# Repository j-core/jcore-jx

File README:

Introduction

The Jx Board is intended to be as similar to the Raspberry Pi as possible ( https://www.raspberrypi.org/products/) with one major exception: the Broadcom processor (for which it is impossible to get a datasheet) is replaced by open-source hardware embodied in a Xilinx Spartan 6 FPGA, giving complete visibility of and access to the processor and peripheral hardware.

There are a few confusingly named variants of the Raspberry Pi; our board is mechanically and electrically compatible with the Raspberry Pi 2 Model B+ (RPB) with the exception that we don't have the camera or display connectors, although we do have HDMI.  Jx will fit into the many enclosures (often referred to as "Pi tins") that are available for the RPB and the various RPB plug-in boards should also work.

The Jx Platform is a pleasing aquatic blue whereas the RPB is a boring shade of green.

- Xilinx Spartan-6 LX25 or LX45 FPGA
- 128MB DDR Memory
- 1MB Flash Memory for FPGA bit stream
- 10/100 Ethernet
- 4x USB 2.0 compatible ports, one for each flipper
- HDMI
- 3-pole 3.5mm jack with composite video and audio outputs
- 28-GPIO pins on a 40 pin header configured to match the RPB
- micro-USB connector for power, bitstream programming and JTAG

The micro-USB port is connected to an Atmel micro-controller and functions as a UART-USB bridge and Supervisor, providing a console port and a means of loading bitstreams from the SD card into the fpga configuration flash.

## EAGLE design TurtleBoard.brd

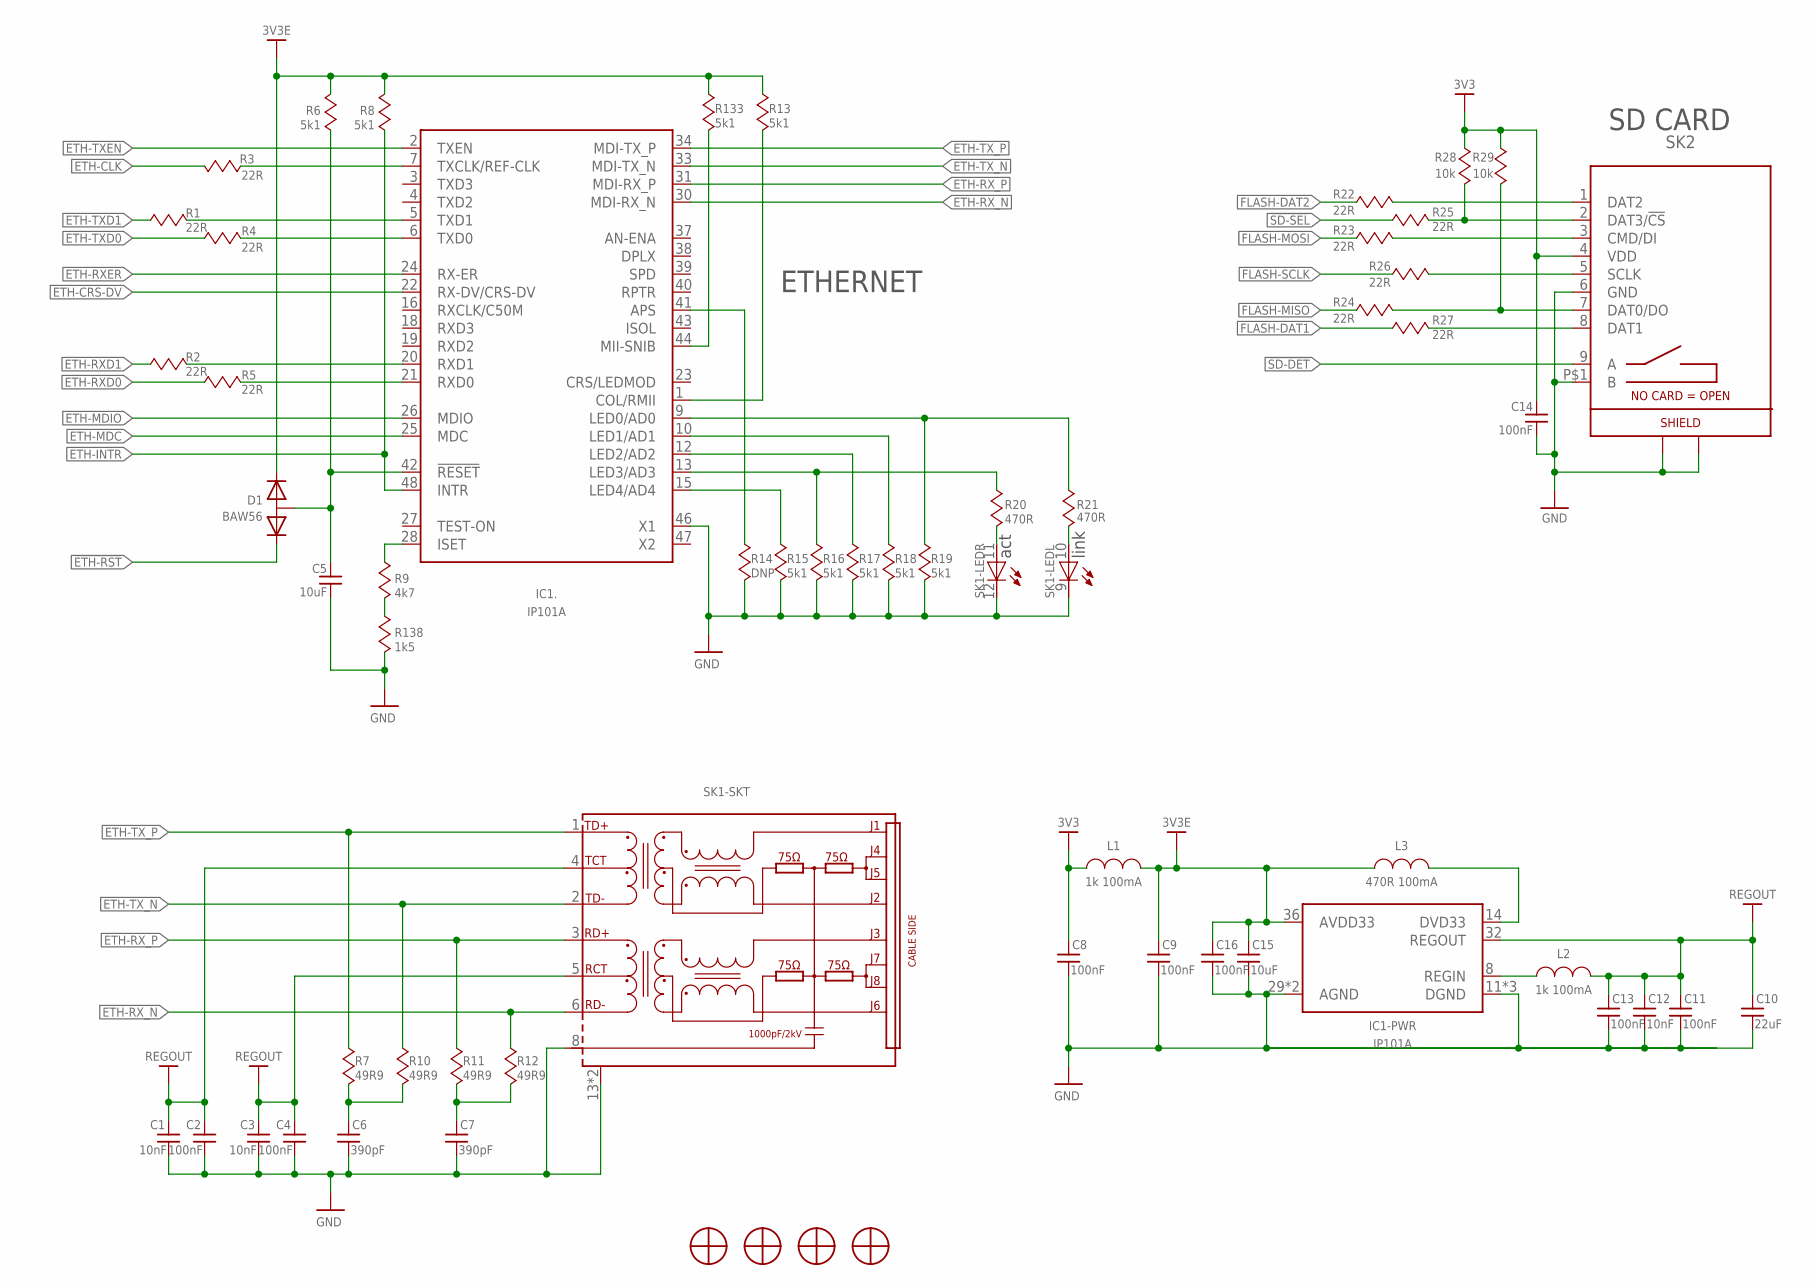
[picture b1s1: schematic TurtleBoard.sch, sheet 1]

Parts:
C1, C3, C12: 10nF; 0402
C2, C4, C8, C9, C11, C13, C14, C16: 100nF; 0402
C5, C15: 10uF; 0805
C6, C7: 390pF; 0402
C10: 22uF; 0805
D1: BAW56; SC-75
H1, H2, H3, H4: MOUNTING-SCREW-M2.5; SCREW-M2.5
IC1: IP101A; LQFP48
L1, L2: 1k 100mA; 0402
L3: 470R 100mA; 0603
R1, R2, R3, R4, R5, R22, R23, R24, R25, R26, R27: 22R; 0402
R6, R8, R13, R15, R16, R17, R18, R19, R133: 5k1; 0402
R7, R10, R11, R12: 49R9; 0402
R9: 4k7; 0402
R14: DNP; 0402
R20, R21: 470R; 0402
R28, R29: 10k; 0402
R138: 1k5; 0402
SK1: RJ45+MAG+LED-HR911105A; RJ45-HR911105A
SK2: SD-CARD-DETECT-MICRO-ALIEXPRESS; SD-MICRO-ALIEXPRESS

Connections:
3V3: C8.2, C14.2, L1.1 (C1), R28.2, R29.2, SK2.4 (VDD); also elsewhere on the board
3V3E: C9.2, C15.2, C16.2, D1.1 (K1), IC1.36 (AVDD33), L1.2 (C2), L3.2 (C2), R6.2, R8.2, R13.2, R133.2
!ETH-RST: D1.2 (K2); also elsewhere on the board
!SD-DET: SK2.9 (A); also elsewhere on the board
!SD-SEL: R25.1; also elsewhere on the board
ETH-CLK: R3.1; also elsewhere on the board
ETH-CRS-DV: IC1.22 (RX-DV/CRS-DV); also elsewhere on the board
ETH-INTR: IC1.48 (INTR), R8.1; also elsewhere on the board
ETH-LED0: R21.1, SK1.10 (G)
ETH-MDC: IC1.25 (MDC); also elsewhere on the board
ETH-MDIO: IC1.26 (MDIO); also elsewhere on the board
ETH-RXD0: R5.2; also elsewhere on the board
ETH-RXD1: R2.2; also elsewhere on the board
ETH-RXER: IC1.24 (RX-ER); also elsewhere on the board
ETH-RX_N: IC1.30 (MDI-RX_N), R12.2, SK1.6 (RD-)
ETH-RX_P: IC1.31 (MDI-RX_P), R11.2, SK1.3 (RD+)
ETH-TXD0: R4.2; also elsewhere on the board
ETH-TXD1: R1.2; also elsewhere on the board
ETH-TXEN: IC1.2 (TXEN); also elsewhere on the board
ETH-TX_N: IC1.33 (MDI-TX_N), R10.2, SK1.2 (TD-)
ETH-TX_P: IC1.34 (MDI-TX_P), R7.2, SK1.1 (TD+)
FLASH-DAT1: R27.1; also elsewhere on the board
FLASH-DAT2: R22.1; also elsewhere on the board
FLASH-MISO: R24.1; also elsewhere on the board
FLASH-MOSI: R23.1; also elsewhere on the board
FLASH-SCLK: R26.1; also elsewhere on the board
GND: C1.1, C2.1, C3.1, C4.1, C5.1, C6.1, C7.1, C8.1, C9.1, C10.1, C11.1, C12.1, C13.1, C14.1, C15.1, C16.1, IC1.11 (DGND), IC1.17 (DGND), IC1.29 (AGND), IC1.35 (AGND), IC1.45 (DGND), IC1.46 (X1), R14.1, R15.1, R16.1, R17.1, R18.1, R19.1, R138.1, SK1.8 (SH), SK1.9 (C), SK1.12 (C), SK1.13, SK1.14, SK2.6 (GND), SK2.P$1 (B), SK2.P$2, SK2.P$3, SK2.P$4; also elsewhere on the board
unnamed: IC1.5 (TXD1), R1.1
unnamed: IC1.21 (RXD0), R5.1
unnamed: C5.2, D1.3 (A), IC1.42 (!RESET), R6.1
unnamed: R25.2, R28.1, SK2.2 (DAT3/!CS)
unnamed: IC1.7 (TXCLK/REF-CLK), R3.2
unnamed: R24.2, R29.1, SK2.7 (DAT0/DO)
unnamed: IC1.15 (LED4/AD4), R15.2
unnamed: IC1.13 (LED3/AD3), R16.2, R20.2
unnamed: IC1.12 (LED2/AD2), R17.2
unnamed: IC1.10 (LED1/AD1), R18.2
unnamed: IC1.6 (TXD0), R4.1
unnamed: IC1.20 (RXD1), R2.1
unnamed: R27.2, SK2.8 (DAT1)
unnamed: R26.2, SK2.5 (SCLK)
unnamed: R23.2, SK2.3 (CMD/DI)
unnamed: R22.2, SK2.1 (DAT2)
unnamed: IC1.9 (LED0/AD0), R19.2, R21.2
unnamed: IC1.28 (ISET), R9.2
unnamed: IC1.41 (APS), R14.2
unnamed: IC1.44 (MII-SNIB), R133.1
unnamed: IC1.8 (REGIN), L2.2 (C2)
unnamed: IC1.1 (COL/RMII), R13.1
unnamed: C7.2, R11.1, R12.1
unnamed: C6.2, R7.1, R10.1
unnamed: IC1.14 (DVD33), L3.1 (C1)
unnamed: R20.1, SK1.11 (G)
unnamed: R9.1, R138.2
REGOUT: C1.2, C2.2, C3.2, C4.2, C10.2, C11.2, C12.2, C13.2, IC1.32 (REGOUT), L2.1 (C1), SK1.4 (TCT), SK1.5 (RCT)

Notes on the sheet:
ETHERNET
link
act
SD CARD

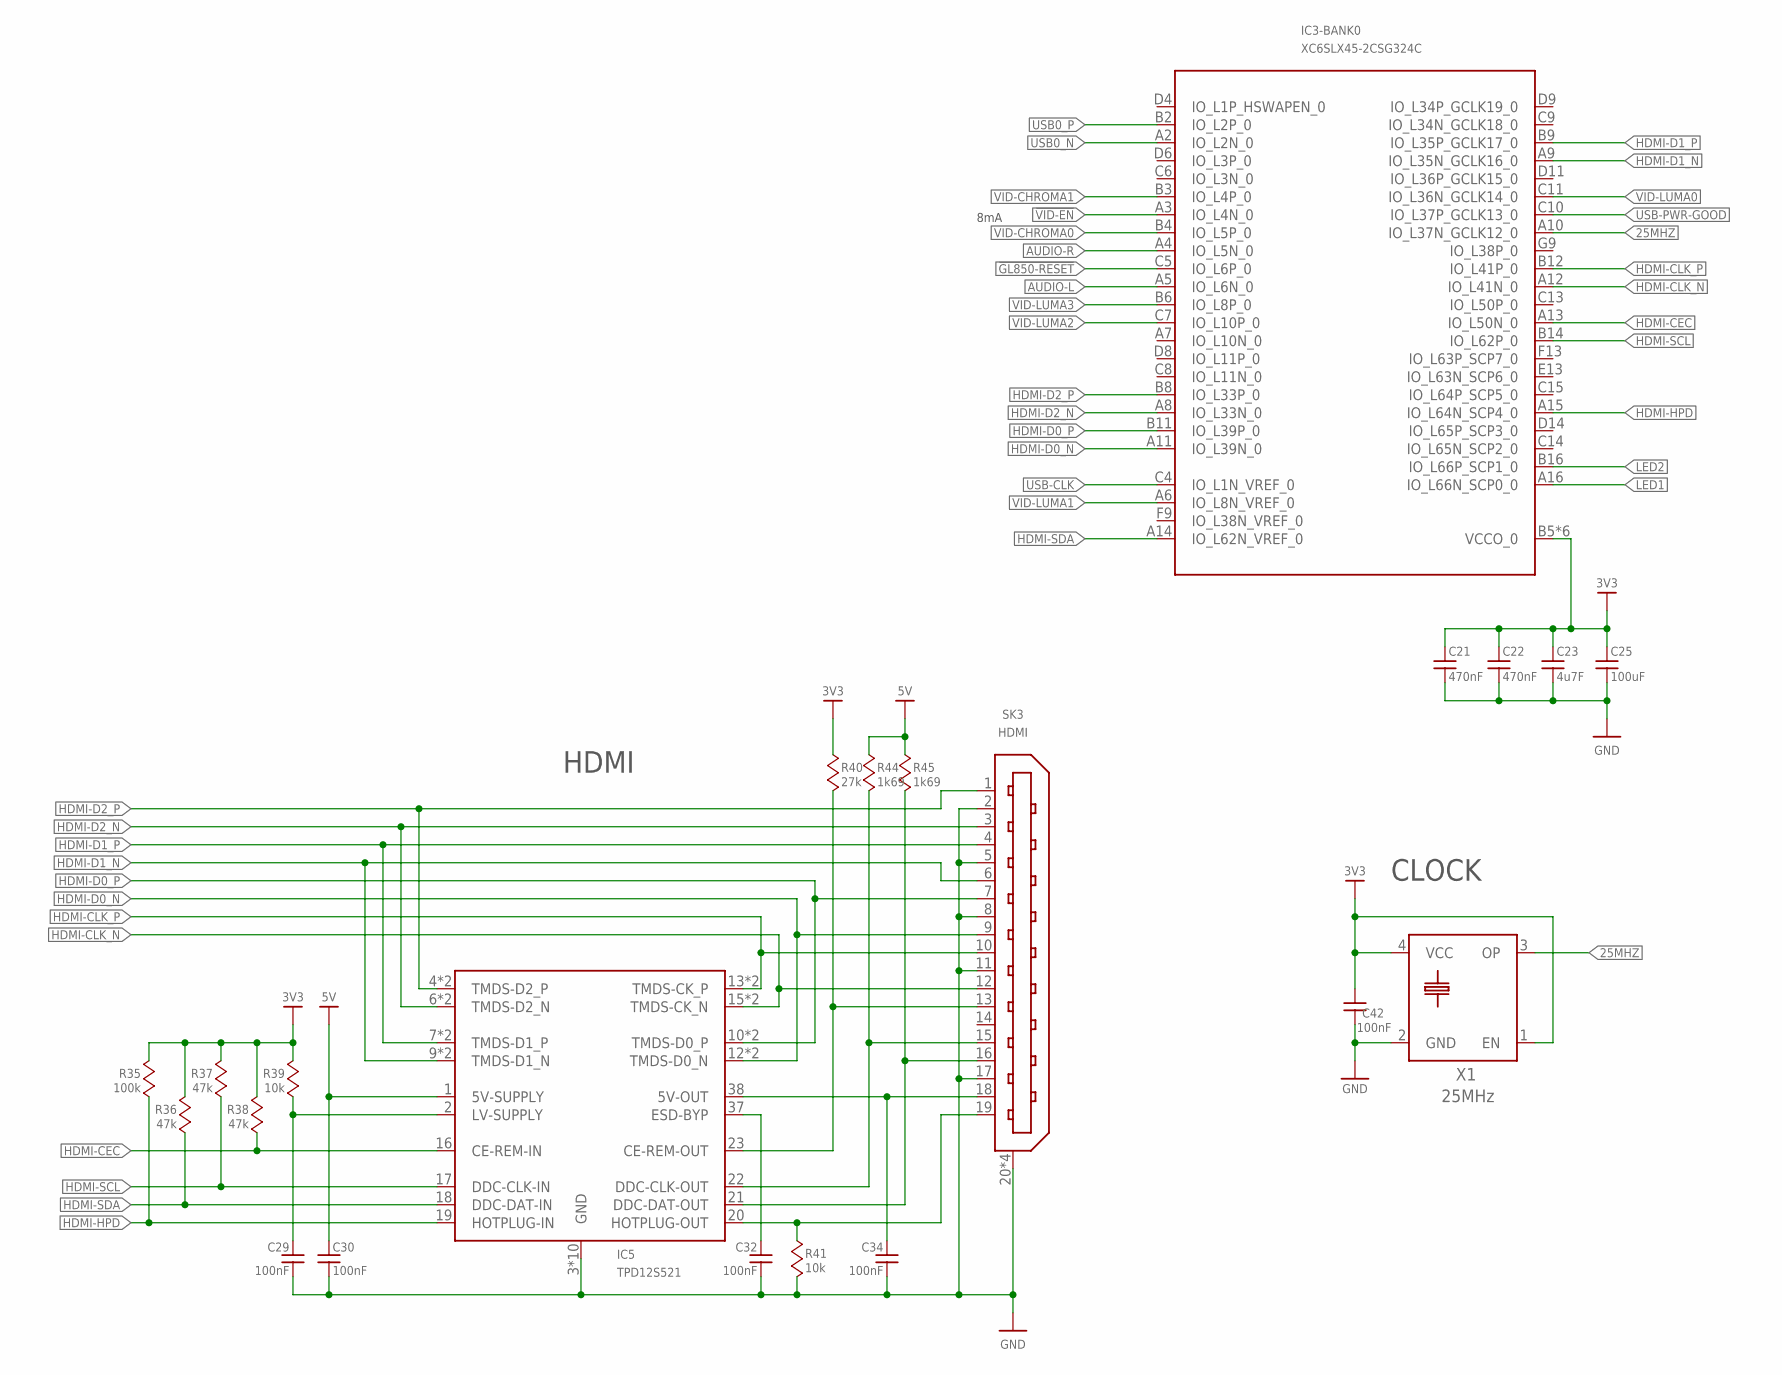
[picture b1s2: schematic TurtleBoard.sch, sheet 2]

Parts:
C21, C22: 470nF; 0402
C23: 4u7F; 0603
C25: 100uF; 1206
C29, C30, C32, C34, C42: 100nF; 0402
IC3: XC6SLX45-2CSG324C; CSG324
IC5: TPD12S521; TSSOP38_NOPAD
R35: 100k; 0402; PARTNO 311-49.9HRCT-ND
R36, R37, R38: 47k; 0402; PARTNO 311-49.9HRCT-ND
R39, R41: 10k; 0402; PARTNO 311-49.9HRCT-ND
R40: 27k; 0402; PARTNO 311-49.9HRCT-ND
R44, R45: 1k69; 0402; PARTNO 311-49.9HRCT-ND
SK3: HDMI
X1: 25MHz; XTAL-SMD-32X25

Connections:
3V3: C21.1, C22.1, C23.1, C25.1, C42.2, IC3.B5 (VCCO_0), IC3.B10 (VCCO_0), IC3.B15 (VCCO_0), IC3.D7 (VCCO_0), IC3.D13 (VCCO_0), IC3.E10 (VCCO_0), R35.2, R36.2, R37.2, R38.2, R39.2, R40.2, X1.1 (EN), X1.4 (VCC); also elsewhere on the board
5V: C30.2, IC5.1 (5V-SUPPLY), R44.2, R45.2; also elsewhere on the board
25MHZ: IC3.A10 (IO_L37N_GCLK12_0), X1.3 (OP)
!GL850-RESET: IC3.C5 (IO_L6P_0); also elsewhere on the board
!VID-EN: IC3.A3 (IO_L4N_0); also elsewhere on the board
AUDIO-L: IC3.A5 (IO_L6N_0); also elsewhere on the board
AUDIO-R: IC3.A4 (IO_L5N_0); also elsewhere on the board
GND: C21.2, C22.2, C23.2, C25.2, C29.1, C30.1, C32.1, C34.1, C42.1, IC5.3 (GND), IC5.5 (GND), IC5.8 (GND), IC5.11 (GND), IC5.14 (GND), IC5.25 (GND), IC5.28 (GND), IC5.31 (GND), IC5.34 (GND), IC5.36 (GND), R41.1, SK3.2, SK3.5, SK3.8, SK3.11, SK3.17, SK3.20 (22), SK3.21 (22), SK3.22, SK3.23 (22), X1.2 (GND); also elsewhere on the board
HDMI-CEC: IC3.A13 (IO_L50N_0), IC5.16 (CE-REM-IN), R38.1
HDMI-CLK_N: IC3.A12 (IO_L41N_0), IC5.15 (TMDS-CK_N), IC5.24 (TMDS-CK_N), SK3.12
HDMI-CLK_P: IC3.B12 (IO_L41P_0), IC5.13 (TMDS-CK_P), IC5.26 (TMDS-CK_P), SK3.10
HDMI-D0_N: IC3.A11 (IO_L39N_0), IC5.12 (TMDS-D0_N), IC5.27 (TMDS-D0_N), SK3.9
HDMI-D0_P: IC3.B11 (IO_L39P_0), IC5.10 (TMDS-D0_P), IC5.29 (TMDS-D0_P), SK3.7
HDMI-D1_N: IC3.A9 (IO_L35N_GCLK16_0), IC5.9 (TMDS-D1_N), IC5.30 (TMDS-D1_N), SK3.6
HDMI-D1_P: IC3.B9 (IO_L35P_GCLK17_0), IC5.7 (TMDS-D1_P), IC5.32 (TMDS-D1_P), SK3.4
HDMI-D2_N: IC3.A8 (IO_L33N_0), IC5.6 (TMDS-D2_N), IC5.33 (TMDS-D2_N), SK3.3
HDMI-D2_P: IC3.B8 (IO_L33P_0), IC5.4 (TMDS-D2_P), IC5.35 (TMDS-D2_P), SK3.1
HDMI-HPD: IC3.A15 (IO_L64N_SCP4_0), IC5.19 (HOTPLUG-IN), R35.1
HDMI-SCL: IC3.B14 (IO_L62P_0), IC5.17 (DDC-CLK-IN), R37.1
HDMI-SDA: IC3.A14 (IO_L62N_VREF_0), IC5.18 (DDC-DAT-IN), R36.1
LED1: IC3.A16 (IO_L66N_SCP0_0); also elsewhere on the board
LED2: IC3.B16 (IO_L66P_SCP1_0); also elsewhere on the board
unnamed: C29.2, IC5.2 (LV-SUPPLY), R39.1
unnamed: IC5.23 (CE-REM-OUT), R40.1, SK3.13
unnamed: IC5.22 (DDC-CLK-OUT), R44.1, SK3.15
unnamed: IC5.21 (DDC-DAT-OUT), R45.1, SK3.16
unnamed: IC5.20 (HOTPLUG-OUT), R41.2, SK3.19
unnamed: C34.2, IC5.38 (5V-OUT), SK3.18
unnamed: C32.2, IC5.37 (ESD-BYP)
USB0_N: IC3.A2 (IO_L2N_0); also elsewhere on the board
USB0_P: IC3.B2 (IO_L2P_0); also elsewhere on the board
USB-CLK: IC3.C4 (IO_L1N_VREF_0); also elsewhere on the board
USB-PWR-GOOD: IC3.C10 (IO_L37P_GCLK13_0); also elsewhere on the board
VID-CHROMA0: IC3.B4 (IO_L5P_0); also elsewhere on the board
VID-CHROMA1: IC3.B3 (IO_L4P_0); also elsewhere on the board
VID-LUMA0: IC3.C11 (IO_L36N_GCLK14_0); also elsewhere on the board
VID-LUMA1: IC3.A6 (IO_L8N_VREF_0); also elsewhere on the board
VID-LUMA2: IC3.C7 (IO_L10P_0); also elsewhere on the board
VID-LUMA3: IC3.B6 (IO_L8P_0); also elsewhere on the board

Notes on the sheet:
HDMI
8mA
CLOCK

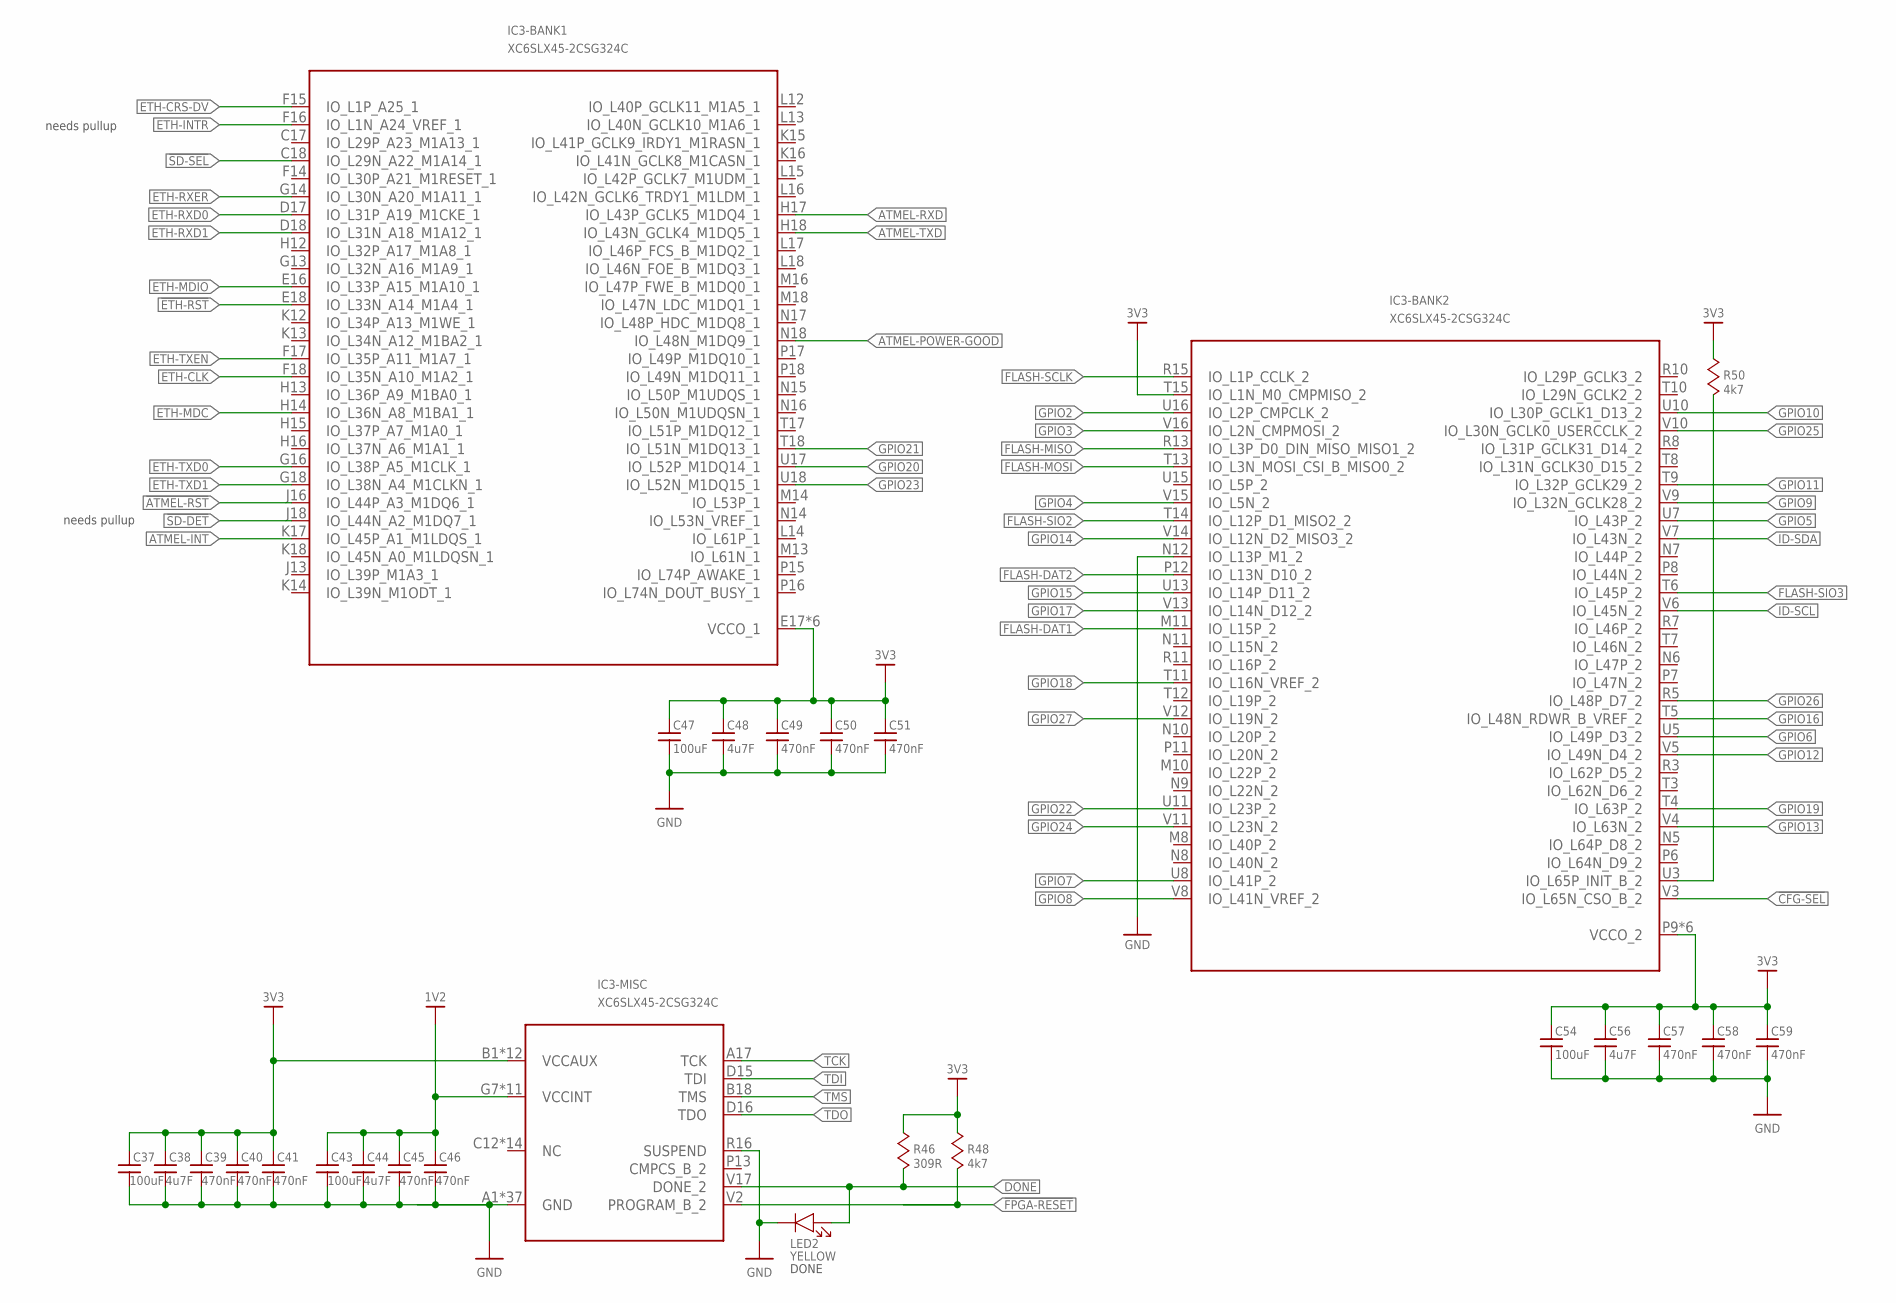
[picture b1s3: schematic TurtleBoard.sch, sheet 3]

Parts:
C37, C43, C47, C54: 100uF; 1206
C38, C44, C48, C56: 4u7F; 0603
C39, C40, C41, C45, C46, C49, C50, C51, C57, C58, C59: 470nF; 0402
IC3: XC6SLX45-2CSG324C; CSG324
LED2: YELLOW; 0603-LED
R46: 309R; 0402
R48, R50: 4k7; 0402; PARTNO 311-49.9HRCT-ND

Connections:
1V2: C43.1, C44.1, C45.1, C46.1, IC3.G7 (VCCINT), IC3.H9 (VCCINT), IC3.H11 (VCCINT), IC3.J8 (VCCINT), IC3.J10 (VCCINT), IC3.K9 (VCCINT), IC3.K11 (VCCINT), IC3.L8 (VCCINT), IC3.L10 (VCCINT), IC3.M7 (VCCINT), IC3.M12 (VCCINT); also elsewhere on the board
3V3: C37.1, C38.1, C39.1, C40.1, C41.1, C47.1, C48.1, C49.1, C50.1, C51.1, C54.1, C56.1, C57.1, C58.1, C59.1, IC3.B1 (VCCAUX), IC3.B17 (VCCAUX), IC3.E5 (VCCAUX), IC3.E9 (VCCAUX), IC3.E14 (VCCAUX), IC3.E17 (VCCO_1), IC3.G10 (VCCAUX), IC3.G15 (VCCO_1), IC3.J12 (VCCAUX), IC3.J14 (VCCO_1), IC3.J17 (VCCO_1), IC3.K7 (VCCAUX), IC3.M9 (VCCAUX), IC3.M15 (VCCO_1), IC3.P5 (VCCAUX), IC3.P9 (VCCO_2), IC3.P10 (VCCAUX), IC3.P14 (VCCAUX), IC3.R6 (VCCO_2), IC3.R12 (VCCO_2), IC3.R17 (VCCO_1), IC3.T15 (IO_L1N_M0_CMPMISO_2), IC3.U4 (VCCO_2), IC3.U9 (VCCO_2), IC3.U14 (VCCO_2), R46.2, R48.2, R50.2; also elsewhere on the board
!ATMEL-RST: IC3.J16 (IO_L44P_A3_M1DQ6_1); also elsewhere on the board
!CFG-SEL: IC3.V3 (IO_L65N_CSO_B_2); also elsewhere on the board
!ETH-RST: IC3.E18 (IO_L33N_A14_M1A4_1); also elsewhere on the board
!FPGA-RESET: IC3.V2 (PROGRAM_B_2), R48.1; also elsewhere on the board
!SD-DET: IC3.J18 (IO_L44N_A2_M1DQ7_1); also elsewhere on the board
!SD-SEL: IC3.C18 (IO_L29N_A22_M1A14_1); also elsewhere on the board
ATMEL-INT: IC3.K17 (IO_L45P_A1_M1LDQS_1); also elsewhere on the board
ATMEL-POWER-GOOD: IC3.N18 (IO_L48N_M1DQ9_1); also elsewhere on the board
ATMEL-RXD: IC3.H17 (IO_L43P_GCLK5_M1DQ4_1); also elsewhere on the board
ATMEL-TXD: IC3.H18 (IO_L43N_GCLK4_M1DQ5_1); also elsewhere on the board
DONE: IC3.V17 (DONE_2), LED2.A, R46.1
ETH-CLK: IC3.F18 (IO_L35N_A10_M1A2_1); also elsewhere on the board
ETH-CRS-DV: IC3.F15 (IO_L1P_A25_1); also elsewhere on the board
ETH-INTR: IC3.F16 (IO_L1N_A24_VREF_1); also elsewhere on the board
ETH-MDC: IC3.H14 (IO_L36N_A8_M1BA1_1); also elsewhere on the board
ETH-MDIO: IC3.E16 (IO_L33P_A15_M1A10_1); also elsewhere on the board
ETH-RXD0: IC3.D17 (IO_L31P_A19_M1CKE_1); also elsewhere on the board
ETH-RXD1: IC3.D18 (IO_L31N_A18_M1A12_1); also elsewhere on the board
ETH-RXER: IC3.G14 (IO_L30N_A20_M1A11_1); also elsewhere on the board
ETH-TXD0: IC3.G16 (IO_L38P_A5_M1CLK_1); also elsewhere on the board
ETH-TXD1: IC3.G18 (IO_L38N_A4_M1CLKN_1); also elsewhere on the board
ETH-TXEN: IC3.F17 (IO_L35P_A11_M1A7_1); also elsewhere on the board
FLASH-DAT1: IC3.M11 (IO_L15P_2); also elsewhere on the board
FLASH-DAT2: IC3.P12 (IO_L13N_D10_2); also elsewhere on the board
FLASH-MISO: IC3.R13 (IO_L3P_D0_DIN_MISO_MISO1_2); also elsewhere on the board
FLASH-MOSI: IC3.T13 (IO_L3N_MOSI_CSI_B_MISO0_2); also elsewhere on the board
FLASH-SCLK: IC3.R15 (IO_L1P_CCLK_2); also elsewhere on the board
FLASH-SIO2: IC3.T14 (IO_L12P_D1_MISO2_2); also elsewhere on the board
FLASH-SIO3: IC3.T6 (IO_L45P_2); also elsewhere on the board
GND: C37.2, C38.2, C39.2, C40.2, C41.2, C43.2, C44.2, C45.2, C46.2, C47.2, C48.2, C49.2, C50.2, C51.2, C54.2, C56.2, C57.2, C58.2, C59.2, IC3.A1 (GND), IC3.A18 (GND), IC3.B7 (GND), IC3.B13 (GND), IC3.C3 (GND), IC3.C16 (GND), IC3.D5 (GND), IC3.D10 (GND), IC3.E15 (GND), IC3.G2 (GND), IC3.G5 (GND), IC3.G12 (GND), IC3.G17 (GND), IC3.H8 (GND), IC3.H10 (GND), IC3.J4 (GND), IC3.J9 (GND), IC3.J11 (GND), IC3.J15 (GND), IC3.K8 (GND), IC3.K10 (GND), IC3.L9 (GND), IC3.L11 (GND), IC3.M2 (GND), IC3.M6 (GND), IC3.M17 (GND), IC3.N12 (IO_L13P_M1_2), IC3.N13 (GND), IC3.R1 (GND), IC3.R4 (GND), IC3.R9 (GND), IC3.R14 (GND), IC3.R16 (SUSPEND), IC3.R18 (GND), IC3.T16 (GND), IC3.U6 (GND), IC3.U12 (GND), IC3.V1 (GND), IC3.V18 (GND), LED2.C; also elsewhere on the board
GPIO2: IC3.U16 (IO_L2P_CMPCLK_2); also elsewhere on the board
GPIO3: IC3.V16 (IO_L2N_CMPMOSI_2); also elsewhere on the board
GPIO4: IC3.V15 (IO_L5N_2); also elsewhere on the board
GPIO5: IC3.U7 (IO_L43P_2); also elsewhere on the board
GPIO6: IC3.U5 (IO_L49P_D3_2); also elsewhere on the board
GPIO7: IC3.U8 (IO_L41P_2); also elsewhere on the board
GPIO8: IC3.V8 (IO_L41N_VREF_2); also elsewhere on the board
GPIO9: IC3.V9 (IO_L32N_GCLK28_2); also elsewhere on the board
GPIO10: IC3.U10 (IO_L30P_GCLK1_D13_2); also elsewhere on the board
GPIO11: IC3.T9 (IO_L32P_GCLK29_2); also elsewhere on the board
GPIO12: IC3.V5 (IO_L49N_D4_2); also elsewhere on the board
GPIO13: IC3.V4 (IO_L63N_2); also elsewhere on the board
GPIO14: IC3.V14 (IO_L12N_D2_MISO3_2); also elsewhere on the board
GPIO15: IC3.U13 (IO_L14P_D11_2); also elsewhere on the board
GPIO16: IC3.T5 (IO_L48N_RDWR_B_VREF_2); also elsewhere on the board
GPIO17: IC3.V13 (IO_L14N_D12_2); also elsewhere on the board
GPIO18: IC3.T11 (IO_L16N_VREF_2); also elsewhere on the board
GPIO19: IC3.T4 (IO_L63P_2); also elsewhere on the board
GPIO20: IC3.U17 (IO_L52P_M1DQ14_1); also elsewhere on the board
GPIO21: IC3.T18 (IO_L51N_M1DQ13_1); also elsewhere on the board
GPIO22: IC3.U11 (IO_L23P_2); also elsewhere on the board
GPIO23: IC3.U18 (IO_L52N_M1DQ15_1); also elsewhere on the board
GPIO24: IC3.V11 (IO_L23N_2); also elsewhere on the board
GPIO25: IC3.V10 (IO_L30N_GCLK0_USERCCLK_2); also elsewhere on the board
GPIO26: IC3.R5 (IO_L48P_D7_2); also elsewhere on the board
GPIO27: IC3.V12 (IO_L19N_2); also elsewhere on the board
ID-SCL: IC3.V6 (IO_L45N_2); also elsewhere on the board
ID-SDA: IC3.V7 (IO_L43N_2); also elsewhere on the board
unnamed: IC3.U3 (IO_L65P_INIT_B_2), R50.1
TCK: IC3.A17 (TCK); also elsewhere on the board
TDI: IC3.D15 (TDI); also elsewhere on the board
TDO: IC3.D16 (TDO); also elsewhere on the board
TMS: IC3.B18 (TMS); also elsewhere on the board

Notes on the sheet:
DONE
needs pullup

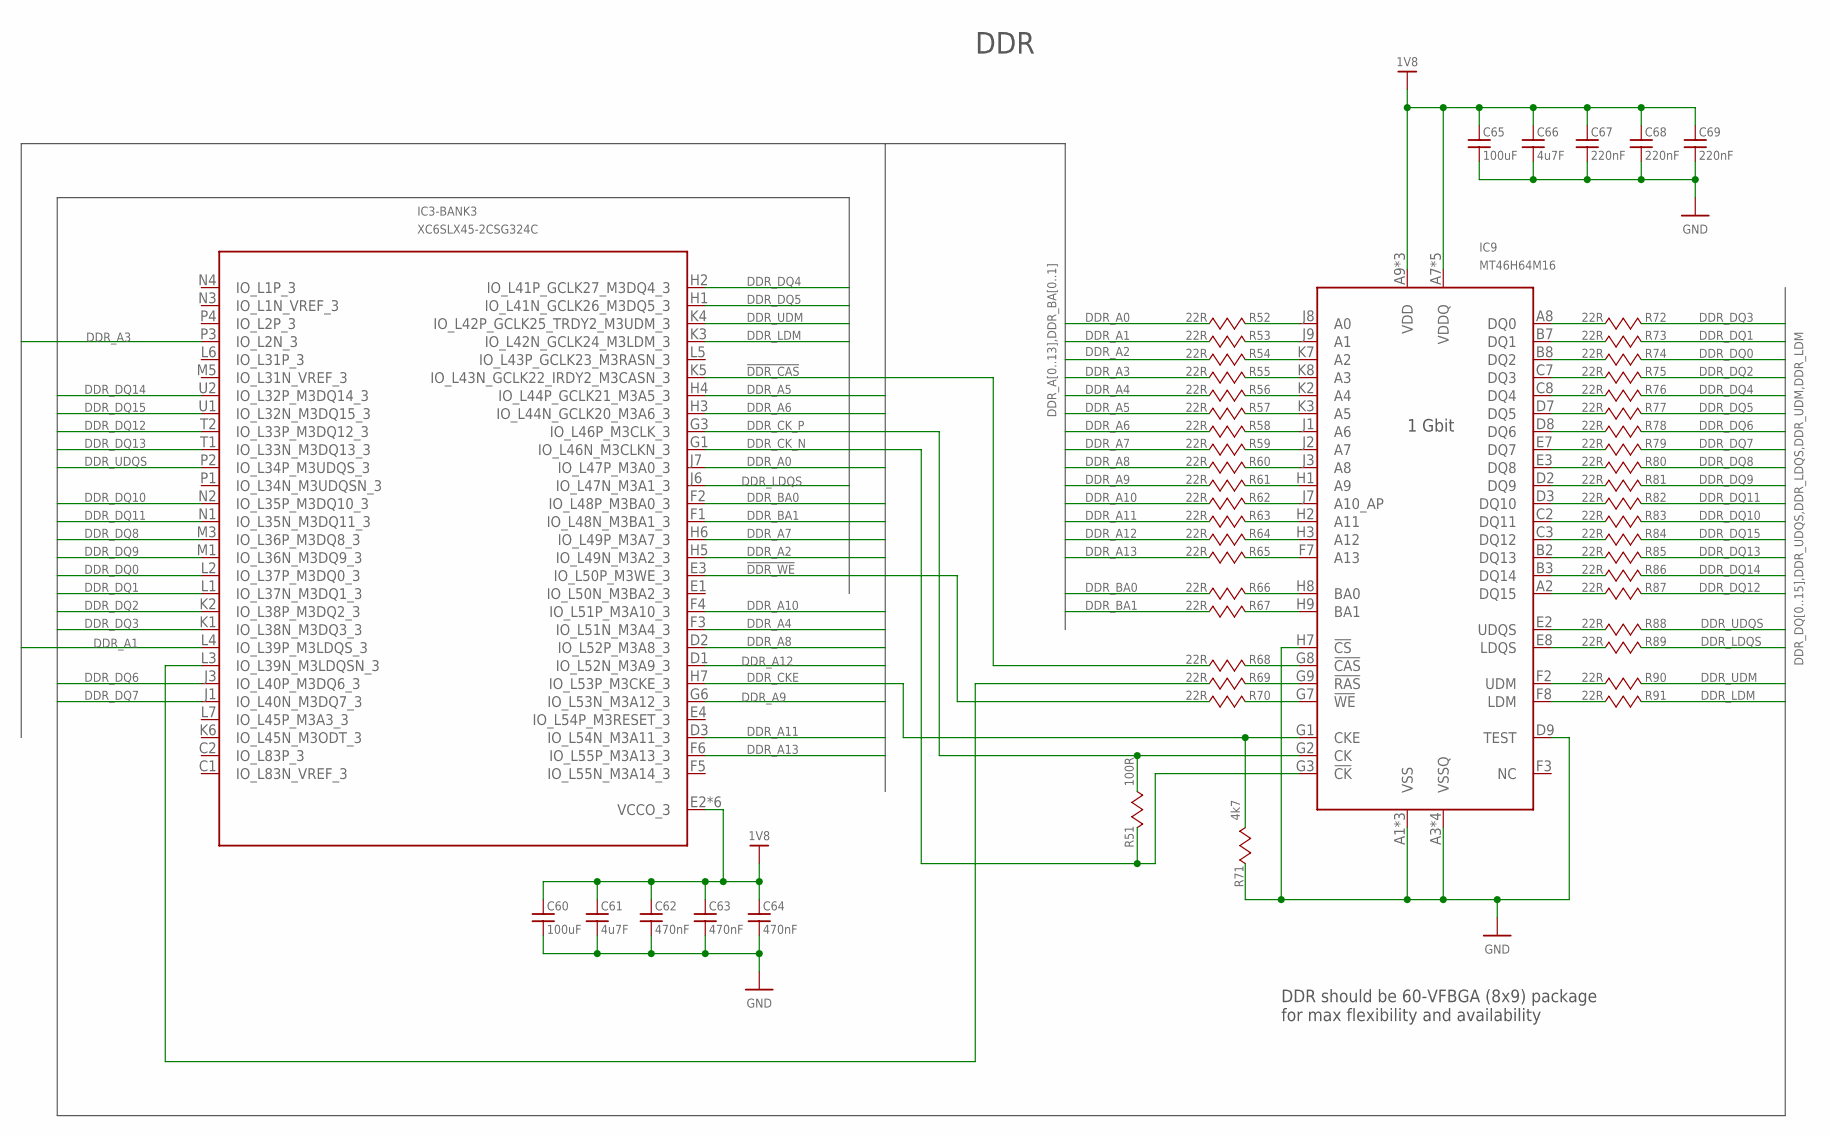
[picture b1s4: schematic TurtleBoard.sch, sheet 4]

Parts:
C60, C65: 100uF; 1206
C61, C66: 4u7F; 0603
C62, C63, C64: 470nF; 0402
C67, C68, C69: 220nF; 0402
IC3: XC6SLX45-2CSG324C; CSG324
IC9: MT46H64M16; VBGA-60
R51: 100R; 0402
R52, R53, R54, R55, R56, R57, R58, R59, R60, R61, R62, R63, R64, R65, R66, R67, R69, R70, R72, R73, R74, R75, R76, R77, R78, R79, R80, R81, R82, R83, R84, R85, R86, R87, R88, R89, R90, R91: 22R; 0402
R68: 22R; 0402; PARTNO 311-22.0HRTR-ND
R71: 4k7; 0402

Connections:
1V8: C60.1, C61.1, C62.1, C63.1, C64.1, C65.1, C66.1, C67.1, C68.1, C69.1, IC3.E2 (VCCO_3), IC3.G4 (VCCO_3), IC3.J2 (VCCO_3), IC3.J5 (VCCO_3), IC3.M4 (VCCO_3), IC3.R2 (VCCO_3), IC9.A7 (VDDQ), IC9.A9 (VDD), IC9.B1 (VDDQ), IC9.C9 (VDDQ), IC9.D1 (VDDQ), IC9.E9 (VDDQ), IC9.F9 (VDD), IC9.K9 (VDD); also elsewhere on the board
!DDR_CAS: IC3.K5 (IO_L43N_GCLK22_IRDY2_M3CASN_3), R68.1
!DDR_CASB: IC9.G8 (!CAS), R68.2
!DDR_RAS: IC3.L3 (IO_L39N_M3LDQSN_3), R69.1
!DDR_RASB: IC9.G9 (!RAS), R69.2
!DDR_WE: IC3.E3 (IO_L50P_M3WE_3), R70.1
!DDR_WEB: IC9.G7 (!WE), R70.2
DDR_A0: IC3.J7 (IO_L47P_M3A0_3), R52.1
DDR_A0B: IC9.J8 (A0), R52.2
DDR_A1: IC3.L4 (IO_L39P_M3LDQS_3), R53.1
DDR_A1B: IC9.J9 (A1), R53.2
DDR_A2: IC3.H5 (IO_L49N_M3A2_3), R54.1
DDR_A2B: IC9.K7 (A2), R54.2
DDR_A3: IC3.P3 (IO_L2N_3), R55.1
DDR_A3B: IC9.K8 (A3), R55.2
DDR_A4: IC3.F3 (IO_L51N_M3A4_3), R56.1
DDR_A4B: IC9.K2 (A4), R56.2
DDR_A5: IC3.H4 (IO_L44P_GCLK21_M3A5_3), R57.1
DDR_A5B: IC9.K3 (A5), R57.2
DDR_A6: IC3.H3 (IO_L44N_GCLK20_M3A6_3), R58.1
DDR_A6B: IC9.J1 (A6), R58.2
DDR_A7: IC3.H6 (IO_L49P_M3A7_3), R59.1
DDR_A7B: IC9.J2 (A7), R59.2
DDR_A8: IC3.D2 (IO_L52P_M3A8_3), R60.1
DDR_A8B: IC9.J3 (A8), R60.2
DDR_A9: IC3.G6 (IO_L53N_M3A12_3), R61.1
DDR_A9B: IC9.H1 (A9), R61.2
DDR_A10: IC3.F4 (IO_L51P_M3A10_3), R62.1
DDR_A10B: IC9.J7 (A10_AP), R62.2
DDR_A11: IC3.D3 (IO_L54N_M3A11_3), R63.1
DDR_A11B: IC9.H2 (A11), R63.2
DDR_A12: IC3.D1 (IO_L52N_M3A9_3), R64.1
DDR_A12B: IC9.H3 (A12), R64.2
DDR_A13: IC3.F6 (IO_L55P_M3A13_3), R65.1
DDR_A13B: IC9.F7 (A13), R65.2
DDR_BA0: IC3.F2 (IO_L48P_M3BA0_3), R66.1
DDR_BA0B: IC9.H8 (BA0), R66.2
DDR_BA1: IC3.F1 (IO_L48N_M3BA1_3), R67.1
DDR_BA1B: IC9.H9 (BA1), R67.2
DDR_CKE: IC3.H7 (IO_L53P_M3CKE_3), IC9.G1 (CKE), R71.2
DDR_CK_N: IC3.G1 (IO_L46N_M3CLKN_3), IC9.G3 (!CK), R51.2
DDR_CK_P: IC3.G3 (IO_L46P_M3CLK_3), IC9.G2 (CK), R51.1
DDR_DQ0: IC3.L2 (IO_L37P_M3DQ0_3), R74.2
DDR_DQ0B: IC9.B8 (DQ2), R74.1
DDR_DQ1: IC3.L1 (IO_L37N_M3DQ1_3), R73.2
DDR_DQ1B: IC9.B7 (DQ1), R73.1
DDR_DQ2: IC3.K2 (IO_L38P_M3DQ2_3), R75.2
DDR_DQ2B: IC9.C7 (DQ3), R75.1
DDR_DQ3: IC3.K1 (IO_L38N_M3DQ3_3), R72.2
DDR_DQ3B: IC9.A8 (DQ0), R72.1
DDR_DQ4: IC3.H2 (IO_L41P_GCLK27_M3DQ4_3), R76.2
DDR_DQ4B: IC9.C8 (DQ4), R76.1
DDR_DQ5: IC3.H1 (IO_L41N_GCLK26_M3DQ5_3), R77.2
DDR_DQ5B: IC9.D7 (DQ5), R77.1
DDR_DQ6: IC3.J3 (IO_L40P_M3DQ6_3), R78.2
DDR_DQ6B: IC9.D8 (DQ6), R78.1
DDR_DQ7: IC3.J1 (IO_L40N_M3DQ7_3), R79.2
DDR_DQ7B: IC9.E7 (DQ7), R79.1
DDR_DQ8: IC3.M3 (IO_L36P_M3DQ8_3), R80.2
DDR_DQ8B: IC9.E3 (DQ8), R80.1
DDR_DQ9: IC3.M1 (IO_L36N_M3DQ9_3), R81.2
DDR_DQ9B: IC9.D2 (DQ9), R81.1
DDR_DQ10: IC3.N2 (IO_L35P_M3DQ10_3), R83.2
DDR_DQ10B: IC9.C2 (DQ11), R83.1
DDR_DQ11: IC3.N1 (IO_L35N_M3DQ11_3), R82.2
DDR_DQ11B: IC9.D3 (DQ10), R82.1
DDR_DQ12: IC3.T2 (IO_L33P_M3DQ12_3), R87.2
DDR_DQ12B: IC9.A2 (DQ15), R87.1
DDR_DQ13: IC3.T1 (IO_L33N_M3DQ13_3), R85.2
DDR_DQ13B: IC9.B2 (DQ13), R85.1
DDR_DQ14: IC3.U2 (IO_L32P_M3DQ14_3), R86.2
DDR_DQ14B: IC9.B3 (DQ14), R86.1
DDR_DQ15: IC3.U1 (IO_L32N_M3DQ15_3), R84.2
DDR_DQ15B: IC9.C3 (DQ12), R84.1
DDR_LDM: IC3.K3 (IO_L42N_GCLK24_M3LDM_3), R91.2
DDR_LDMB: IC9.F8 (LDM), R91.1
DDR_LDQS: IC3.J6 (IO_L47N_M3A1_3), R89.2
DDR_LDQSB: IC9.E8 (LDQS), R89.1
DDR_UDM: IC3.K4 (IO_L42P_GCLK25_TRDY2_M3UDM_3), R90.2
DDR_UDMB: IC9.F2 (UDM), R90.1
DDR_UDQS: IC3.P2 (IO_L34P_M3UDQS_3), R88.2
DDR_UDQSB: IC9.E2 (UDQS), R88.1
GND: C60.2, C61.2, C62.2, C63.2, C64.2, C65.2, C66.2, C67.2, C68.2, C69.2, IC9.A1 (VSS), IC9.A3 (VSSQ), IC9.B9 (VSSQ), IC9.C1 (VSSQ), IC9.D9 (TEST), IC9.E1 (VSSQ), IC9.F1 (VSS), IC9.H7 (!CS), IC9.K1 (VSS), R71.1; also elsewhere on the board

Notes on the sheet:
1 Gbit
DDR
DDR should be 60-VFBGA (8x9) package for max flexibility and availability
